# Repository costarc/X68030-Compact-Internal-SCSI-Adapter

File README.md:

Rev 2.0
- Changes to pinout in the X68000 side, as the 2.0mm pin header seem to use a non standard pinout

Rev 1.0
- Based on SCSI pinouts

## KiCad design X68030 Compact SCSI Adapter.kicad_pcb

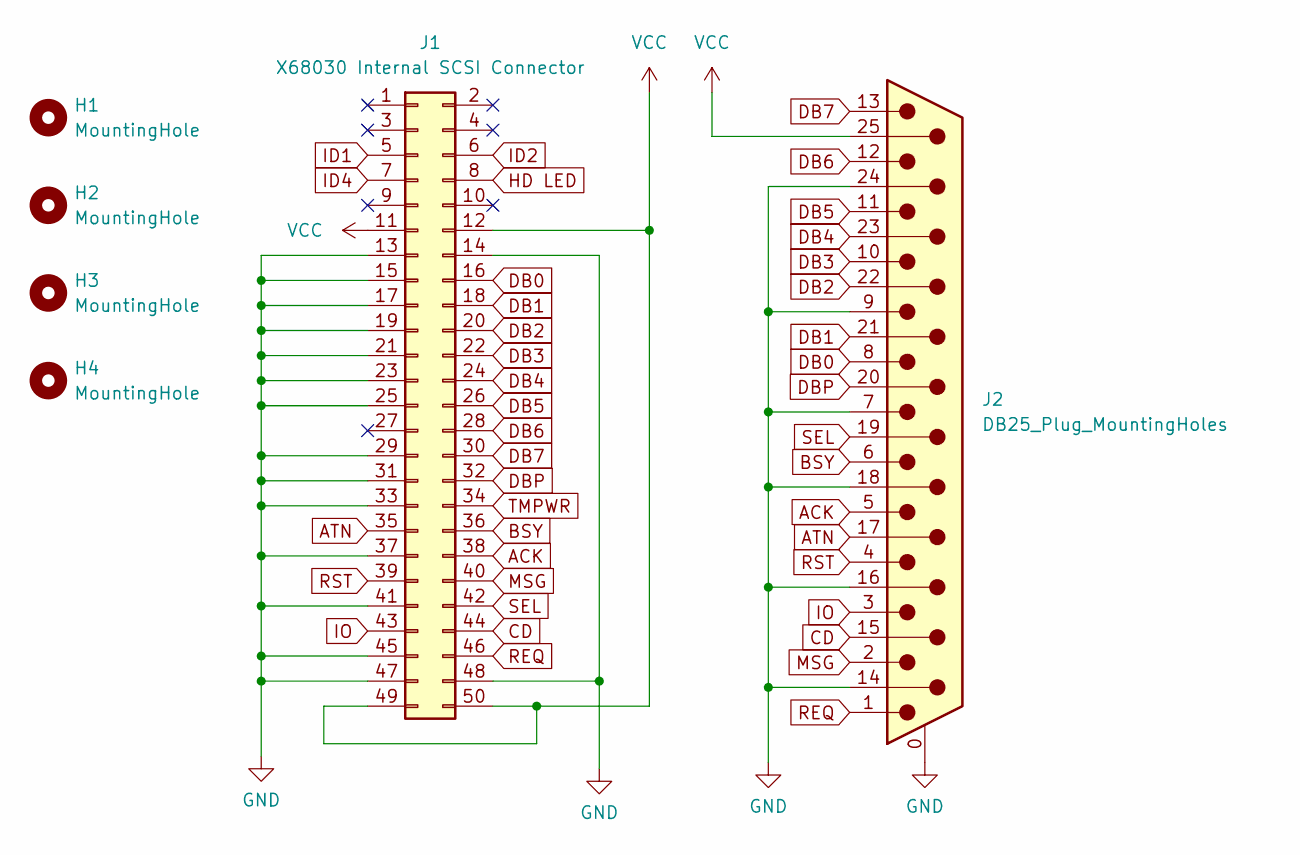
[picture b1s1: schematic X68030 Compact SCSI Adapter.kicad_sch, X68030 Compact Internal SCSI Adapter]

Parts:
H1, H2: MountingHole; MountingHole_3.5mm_Pad
H3, H4: MountingHole; MountingHole_2.1mm
J1: X68030 Internal SCSI Connector; PinSocket_2x25_P2.00mm_Vertical
J2: DB25_Plug_MountingHoles; DSUB-25_Female_Horizontal_P2.77x2.84mm_EdgePinOffset7.70mm_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

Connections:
ACK: J1.38, J2.5
ATN: J1.35, J2.17
BSY: J1.36, J2.6
CD: J1.44, J2.15
DB0: J1.16, J2.8
DB1: J1.18, J2.21
DB2: J1.20, J2.22
DB3: J1.22, J2.10
DB4: J1.24, J2.23
DB5: J1.26, J2.11
DB6: J1.28, J2.12
DB7: J1.30, J2.13
DBP: J1.32, J2.20
GND: J1.13, J1.14, J1.15, J1.17, J1.19, J1.21, J1.23, J1.25, J1.29, J1.31, J1.33, J1.37, J1.41, J1.45, J1.47, J1.48, J2.0 (PAD), J2.7, J2.9, J2.14, J2.16, J2.18, J2.24
HD LED: J1.8
ID1: J1.5
ID2: J1.6
ID4: J1.7
IO: J1.43, J2.3
MSG: J1.40, J2.2
REQ: J1.46, J2.1
RST: J1.39, J2.4
SEL: J1.42, J2.19
TMPWR: J1.34
VCC: J1.11, J1.12, J1.49, J1.50, J2.25

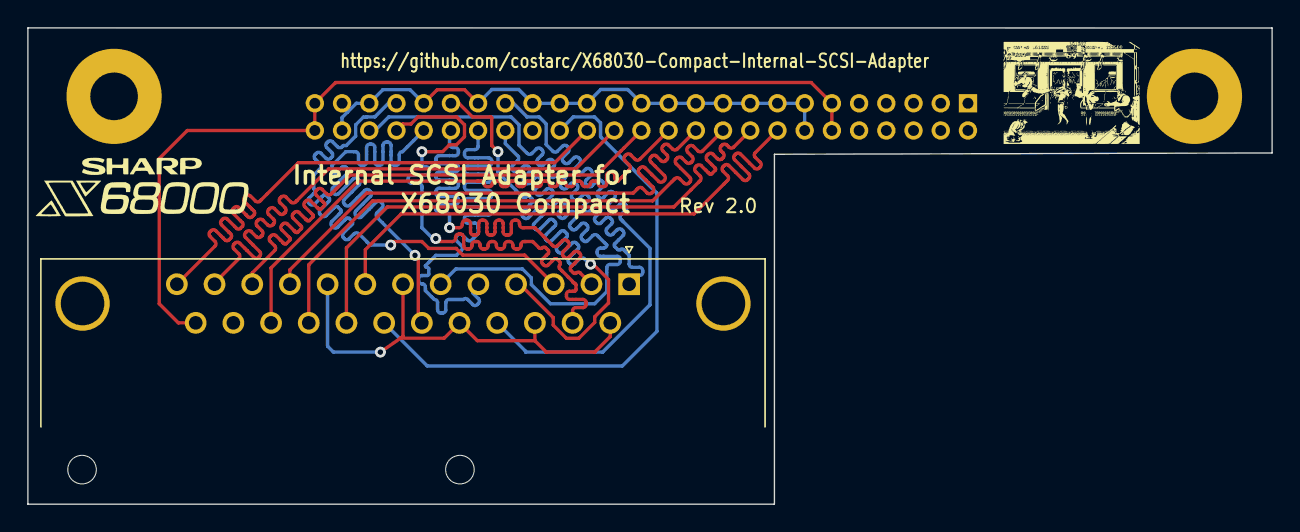
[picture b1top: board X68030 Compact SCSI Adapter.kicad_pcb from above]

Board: 2 copper layers, 91.4 x 35.0 mm, 6 parts (1 on the bottom side), 20 nets.

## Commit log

2024-09-07 Rev. 0
2024-09-07 Rev 1.0 - verified to fit
2024-09-07 Fabricated
2024-09-15 add pinout file
2024-09-16 Rev 2.0
2024-09-17 Fabricated Rev 2.0 with pinout based on CZ-147 Service Manual for X68030 Compact
